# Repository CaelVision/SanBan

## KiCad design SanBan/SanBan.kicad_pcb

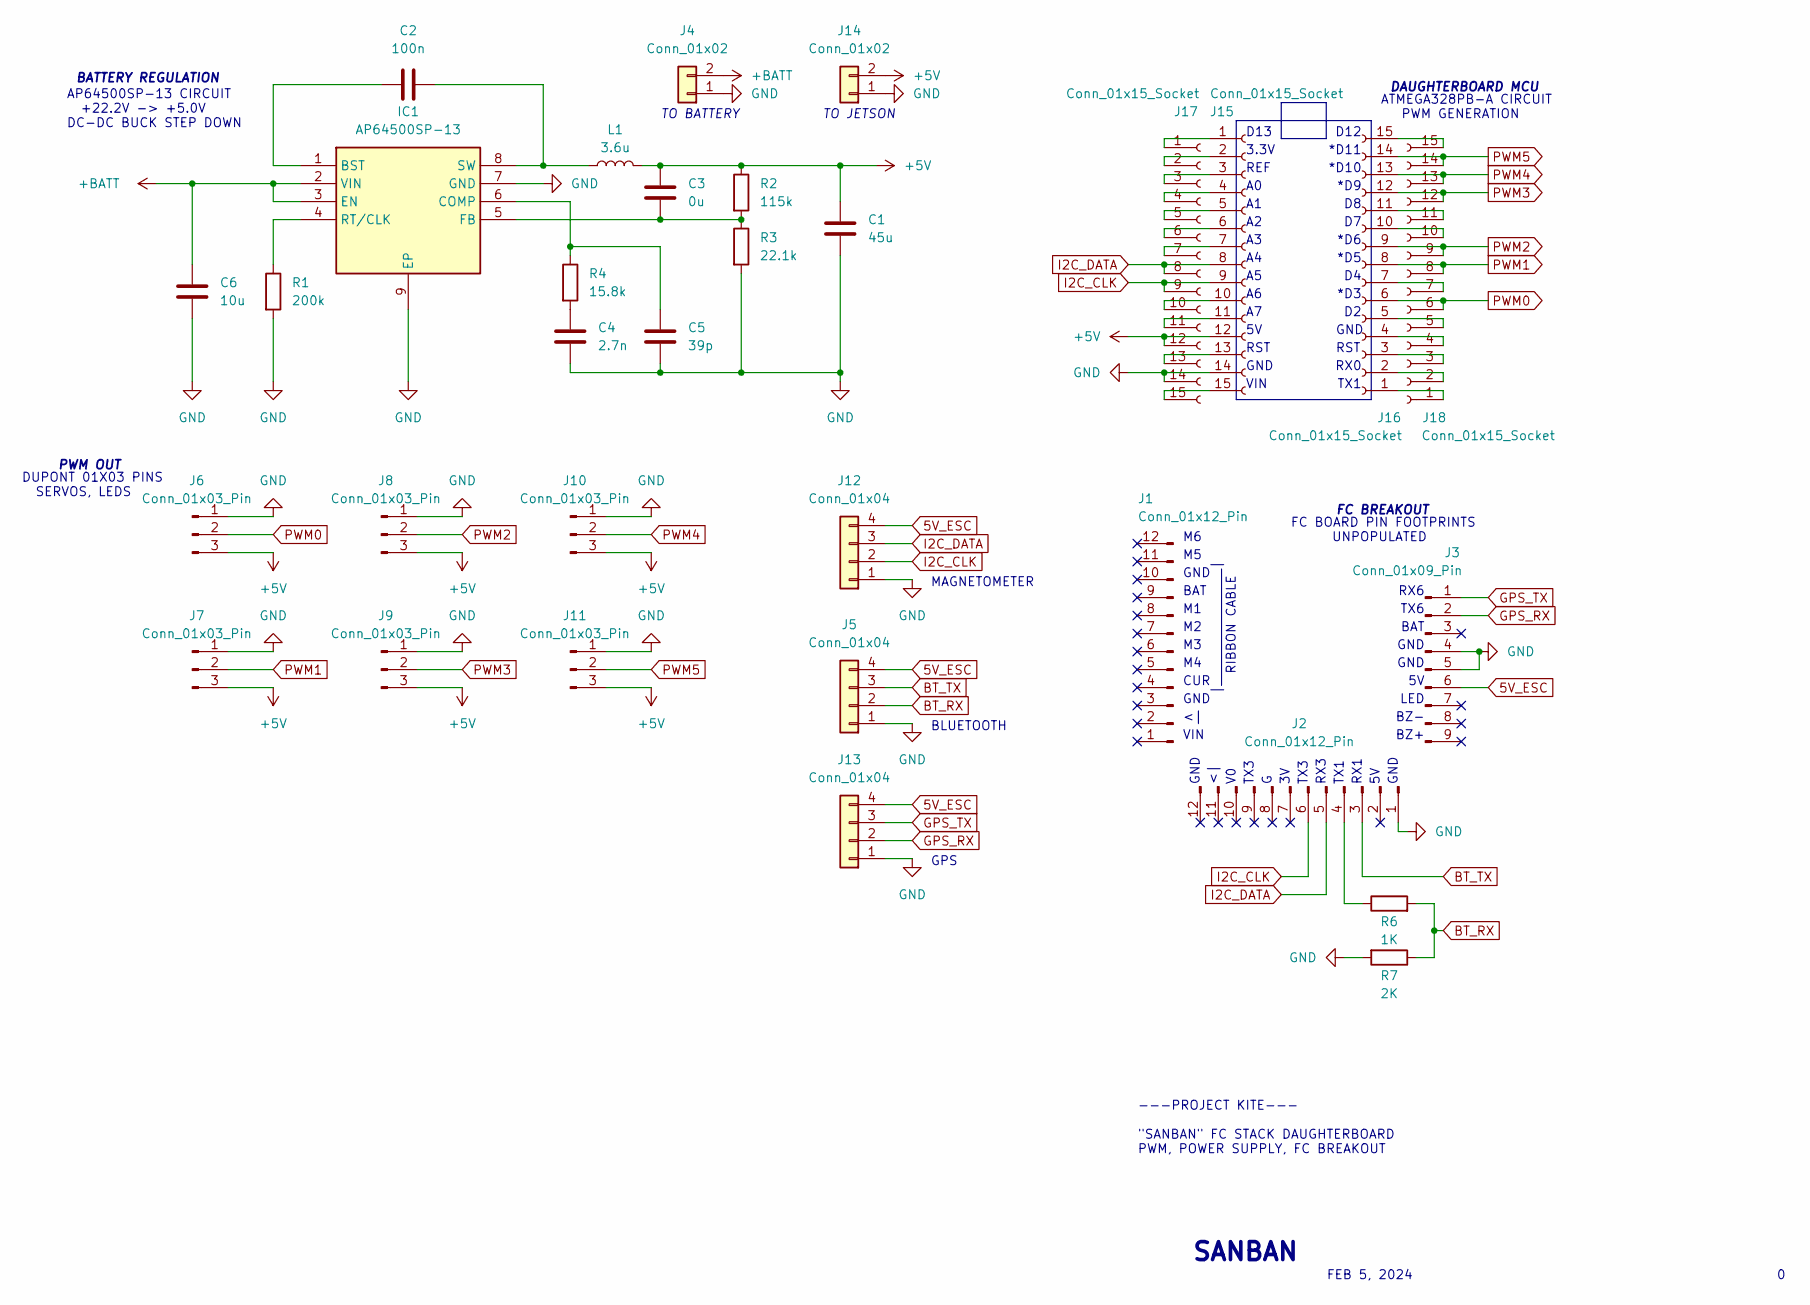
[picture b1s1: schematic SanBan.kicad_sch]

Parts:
C1: 45u; C_0805_2012Metric_Pad1.18x1.45mm_HandSolder
C2: 100n; C_0805_2012Metric_Pad1.18x1.45mm_HandSolder
C3: 0u; C_0805_2012Metric_Pad1.18x1.45mm_HandSolder
C4: 2.7n; C_0805_2012Metric_Pad1.18x1.45mm_HandSolder
C5: 39p; C_0805_2012Metric_Pad1.18x1.45mm_HandSolder
C6: 10u; C_0805_2012Metric_Pad1.18x1.45mm_HandSolder
IC1: AP64500SP-13; SOIC127P600X163-9N; Manufacturer_Part_Number AP64500SP-13; Mouser Part Number 621-AP64500SP-13
J1, J2: Conn_01x12_Pin; PinSocket_1x12_P2.00mm_Vertical
J3: Conn_01x09_Pin; PinSocket_1x09_P2.54mm_Vertical
J4: Conn_01x02; PinHeader_1x02_P2.54mm_Horizontal
J5, J12, J13: Conn_01x04; JST_EH_B4B-EH-A_1x04_P2.50mm_Vertical
J6, J7, J8, J9, J10, J11: Conn_01x03_Pin; PinHeader_1x03_P2.54mm_Vertical
J14: Conn_01x02; JST_EH_B2B-EH-A_1x02_P2.50mm_Vertical
J15, J16, J17, J18: Conn_01x15_Socket; PinSocket_1x15_P2.54mm_Vertical
L1: 3.6u; L_TDK_VLS6045EX_VLS6045AF
R1: 200k; C_0805_2012Metric_Pad1.18x1.45mm_HandSolder
R2: 115k; C_0805_2012Metric_Pad1.18x1.45mm_HandSolder
R3: 22.1k; C_0805_2012Metric_Pad1.18x1.45mm_HandSolder
R4: 15.8k; C_0805_2012Metric_Pad1.18x1.45mm_HandSolder
R6: 1K; C_0805_2012Metric_Pad1.18x1.45mm_HandSolder
R7: 2K; C_0805_2012Metric_Pad1.18x1.45mm_HandSolder

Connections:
5V_ESC: J3.6, J5.4, J12.4, J13.4
+5V: C1.1, C3.2, J6.3, J7.3, J8.3, J9.3, J10.3, J11.3, J14.2, J15.12, J17.12, L1.2, R2.1
+BATT: C6.2, IC1.2 (VIN), IC1.3 (EN), J4.2
BT_RX: J5.2, R6.2, R7.1
BT_TX: J2.3, J5.3
GND: C1.2, C4.1, C5.1, C6.1, IC1.7 (GND), IC1.9 (EP), J2.1, J3.4, J3.5, J4.1, J5.1, J6.1, J7.1, J8.1, J9.1, J10.1, J11.1, J12.1, J13.1, J14.1, J15.14, J17.14, R1.2, R3.2, R7.2
GPS_RX: J3.2, J13.2
GPS_TX: J3.1, J13.3
I2C_CLK: J2.6, J12.2, J15.9, J17.9
I2C_DATA: J2.5, J12.3, J15.8, J17.8
unnamed: C4.2, R4.2
unnamed: C2.1, IC1.1 (BST)
unnamed: C5.2, IC1.6 (COMP), R4.1
unnamed: C3.1, IC1.5 (FB), R2.2, R3.1
unnamed: IC1.4 (RT/CLK), R1.1
unnamed: C2.2, IC1.8 (SW), L1.1
unnamed: J2.4, R6.1
unnamed: J15.1, J17.1
unnamed: J15.2, J17.2
unnamed: J15.3, J17.3
unnamed: J15.4, J17.4
unnamed: J15.5, J17.5
unnamed: J15.6, J17.6
unnamed: J15.7, J17.7
unnamed: J15.10, J17.10
unnamed: J15.11, J17.11
unnamed: J15.13, J17.13
unnamed: J15.15, J17.15
unnamed: J16.1, J18.1
unnamed: J16.2, J18.2
unnamed: J16.3, J18.3
unnamed: J16.4, J18.4
unnamed: J16.5, J18.5
unnamed: J16.7, J18.7
unnamed: J16.10, J18.10
unnamed: J16.11, J18.11
unnamed: J16.15, J18.15
PWM0: J6.2, J16.6, J18.6
PWM1: J7.2, J16.8, J18.8
PWM2: J8.2, J16.9, J18.9
PWM3: J9.2, J16.12, J18.12
PWM4: J10.2, J16.13, J18.13
PWM5: J11.2, J16.14, J18.14

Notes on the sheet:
*D9
TX3
GPS
GND
DUPONT 01X03 PINS SERVOS, LEDS
3.3V
MAGNETOMETER
*D11
CUR
LED
RX6
*D5
RST
BAT
|_________________| RIBBON CABLE
TX1
DAUGHTERBOARD MCU
D12
VIN
RX3
*D3
AP64500SP-13 CIRCUIT +22.2V -> +5.0V DC-DC BUCK STEP DOWN
REF
PWM OUT
BZ-
FC BREAKOUT
FEB 5, 2024
---PROJECT KITE--- "SANBAN" FC STACK DAUGHTERBOARD PWM, POWER SUPPLY, FC BREAKOUT
BLUETOOTH
D13
TO JETSON
TX6
FC BOARD PIN FOOTPRINTS UNPOPULATED
*D6
ATMEGA328PB-A CIRCUIT PWM GENERATION
RX1
TO BATTERY
BZ+
*D10
BATTERY REGULATION

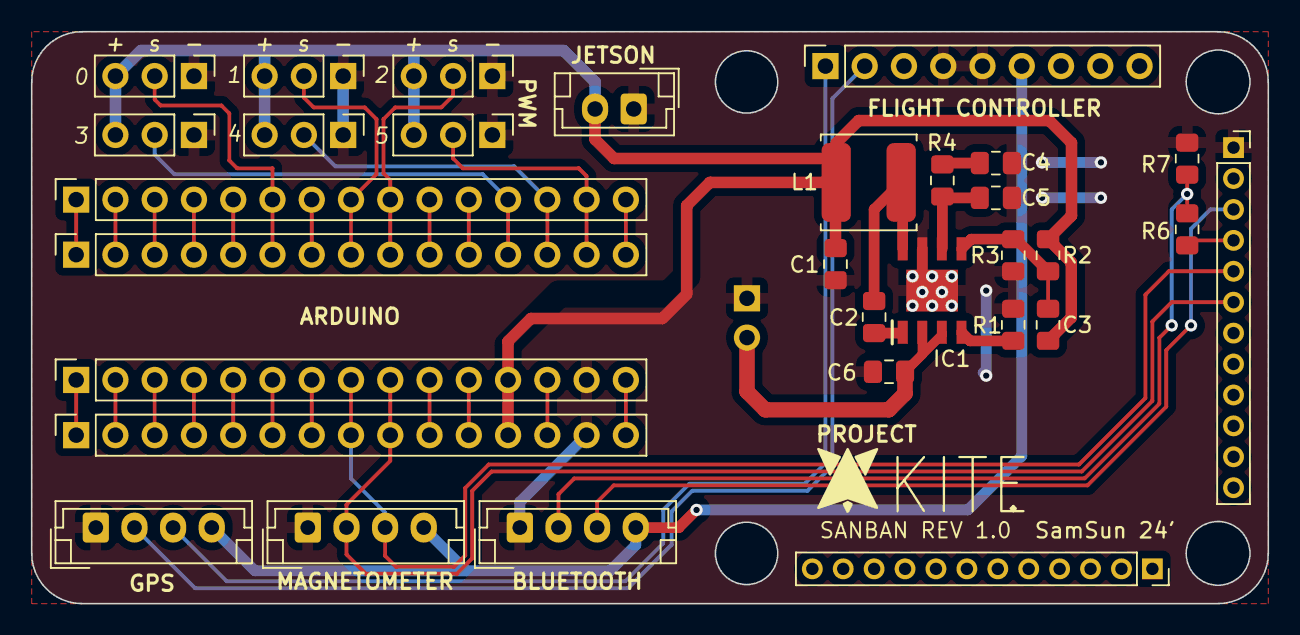
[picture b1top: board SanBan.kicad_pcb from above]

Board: 2 copper layers, 80.0 x 37.0 mm, 32 parts (1 on the bottom side), 43 nets.

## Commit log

2024-01-27 Initial project start
2024-02-05 First pass - added MCU, 5V PS
2024-02-06 Round 2 added FC pinouts
2024-02-06 Started PCB layout
2024-02-12 SanBan Rev 1.0
2024-02-26 Submitted Rev 1 SanBan
